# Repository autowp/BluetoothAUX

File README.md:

# BluetoothAUX

Tiny Bluetooth to AUX converter on CSR8645 and TPA6132A2

Features:
- Size: 23mm x 25mm
- 3.5mm jack output
- Power via micro-USB

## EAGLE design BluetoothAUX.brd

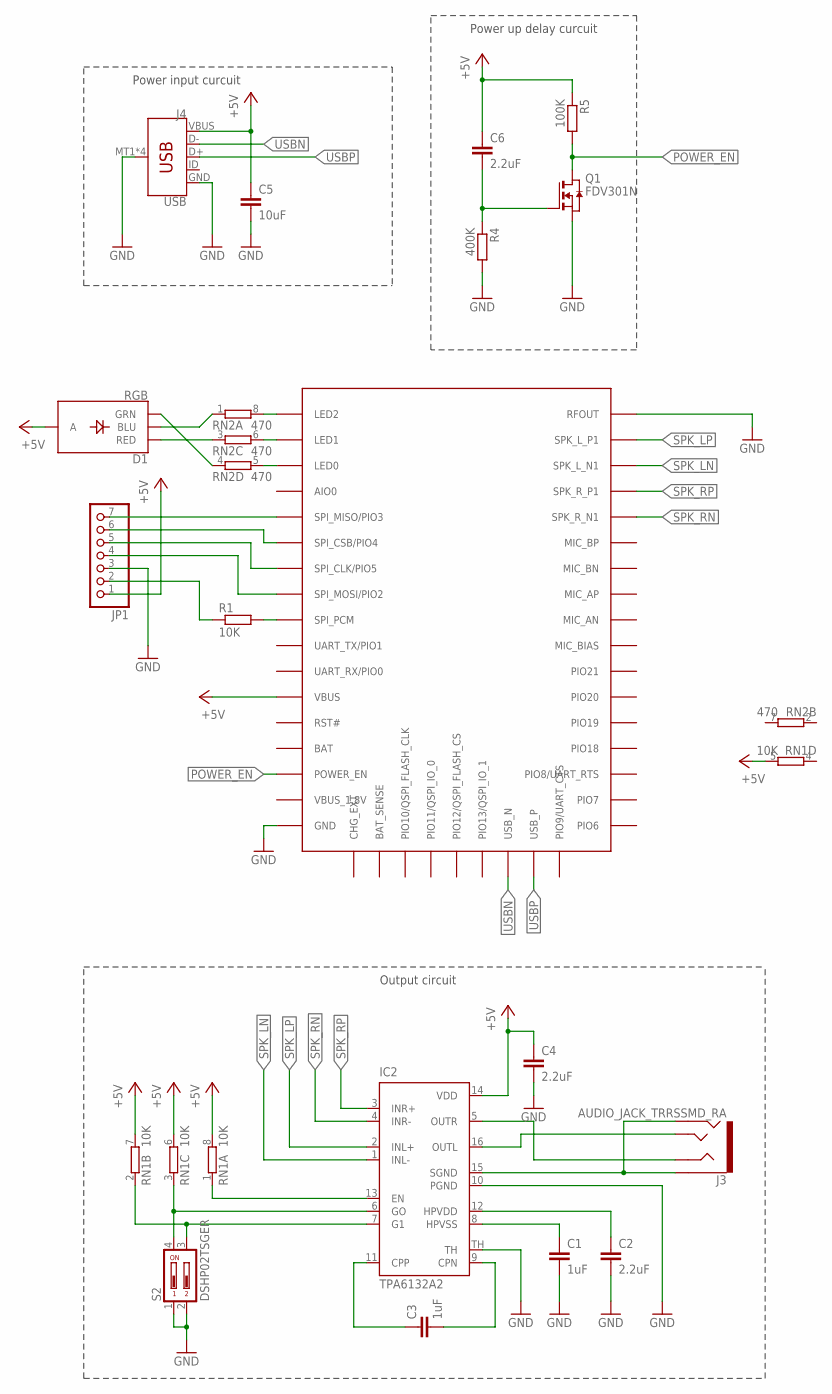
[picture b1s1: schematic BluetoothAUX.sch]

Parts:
C1, C3: 1uF; C0603
C2, C4, C6: 2.2uF; C0603
C5: 10uF; C1206
D1: RGB; P-LCC-4-3
IC2: TPA6132A2; QFN16
J3: AUDIO_JACK_TRRSSMD_RA; AUDIO_JACK_3.5MM_TRRS_SMD_RA
J4: USB; USB-MICROB
JP1: PINHD-1X7; 1X07
Q1: FDV301N; SOT-23
R1: 10K; R0603
R4: 400K; R0603
R5: 100K; R0603
RN1: 10K; 0603-ARC
RN2: 470; 0603-ARC
S2: DSHP02TSGER
U$1: F3188

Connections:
+5V: C4.1, C5.1, C6.1, D1.4 (A), IC2.14 (VDD), J4.VBUS, JP1.1, R5.1, RN1.5 (2), RN1.6 (2), RN1.7 (2), RN1.8 (2), U$1.P$12 (VBUS)
BAT: U$1.P$14 (BAT)
BLUE: RN2.8 (2), U$1.P$1 (LED2)
CLK: JP1.5, U$1.P$7 (SPI_CLK/PIO5)
CPN: C3.2, IC2.9 (CPN)
CPP: C3.1, IC2.11 (CPP)
CS: JP1.6, U$1.P$6 (SPI_CSB/PIO4)
G0: IC2.6 (GO), RN1.3 (1), S2.4
G1: IC2.7 (G1), RN1.2 (1), S2.3
GND: C1.2, C2.2, C4.2, C5.2, IC2.10 (PGND), IC2.TH, J4.GND, J4.MT1 (SHIELD), J4.MT2 (SHIELD), J4.P$1 (SHIELD), J4.P$2 (SHIELD), JP1.3, Q1.P$2 (S), R4.2, S2.1, S2.2, U$1.P$17 (GND), U$1.P$43 (RFOUT)
GREEN: RN2.5 (2), U$1.P$3 (LED0)
HPVSS: C1.1, IC2.8 (HPVSS)
HVPDD: C2.1, IC2.12 (HPVDD)
MISO: JP1.7, U$1.P$5 (SPI_MISO/PIO3)
MOSI: JP1.4, U$1.P$8 (SPI_MOSI/PIO2)
unnamed: R1.2, U$1.P$9 (SPI_PCM)
unnamed: D1.2 (GRN), RN2.4 (1)
unnamed: D1.1 (RED), RN2.3 (1)
unnamed: D1.3 (BLU), RN2.1
unnamed: C6.2, Q1.P$1 (G), R4.1
unnamed: JP1.2, R1.1
OUTL: IC2.16 (OUTL), J3.TIP
OUTR: IC2.5 (OUTR), J3.RING1
POWER_EN: Q1.P$3 (D), R5.2, U$1.P$15 (POWER_EN)
RED: RN2.6 (2), U$1.P$2 (LED1)
SGND: IC2.15 (SGND), J3.EARTH, J3.RING2
SPK_LN: IC2.1 (INL-), U$1.P$41 (SPK_L_N1)
SPK_LP: IC2.2 (INL+), U$1.P$42 (SPK_L_P1)
SPK_RN: IC2.4 (INR-), U$1.P$39 (SPK_R_N1)
SPK_RP: IC2.3 (INR+), U$1.P$40 (SPK_R_P1)
TPA_EN: IC2.13 (EN), RN1.1
USBN: J4.D-, U$1.P$24 (USB_N)
USBP: J4.D+, U$1.P$25 (USB_P)
VBUS_1.8V: U$1.P$16 (VBUS_1.8V)

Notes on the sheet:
Power up delay curcuit
Power input curcuit
Output circuit

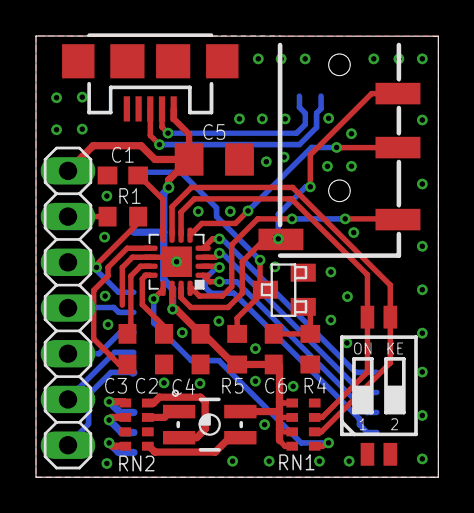
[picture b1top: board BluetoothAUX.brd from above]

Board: 2 copper layers, 22.4 x 24.5 mm, 19 parts (1 on the bottom side), 32 nets.

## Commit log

2017-09-12 First version
2017-09-12 Add trimmers
2017-09-14 Drop DCDC for direct USB supply
2017-09-14 TPA6132A
2017-09-14 LEDs
2017-09-14 Proper RN symbols
2017-09-15 Remove unused COM pin
2017-09-16 Make smaller
2017-09-16 Drill size to .3mm
2017-09-18 VBAT_SENSE, POWER_EN, LEDs
    Connect VBAT_SENSE to BAT
    Delay on POWER_EN
    Swap LED colors
2017-09-18 Route
2017-09-19 Delay circuit with MOSFET
2017-09-20 SPI_PCM resistor
2017-10-17 DIP switch, 4-pin LED, Powerup fix
2017-10-17 Remove UART, add silk
2017-10-17 Improve silk
2017-10-17 Apply Smart Prototyping DRC
2017-11-13 silk update

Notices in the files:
parts and their libraries:
SparkFun-Connectors: Licensing: Creative Commons ShareAlike 4.0 International - https://creativecommons.org/licenses/by-sa/4.0
